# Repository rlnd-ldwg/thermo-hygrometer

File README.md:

# thermo-hygrometer
Thermo-Hygrometer based on DHT22, ATtiny13 and HD44780 compatible display  

v 1.0.3 wrong indication of negative temperature corrected,
pinout change for better use of IPS header for enhancements,
adaptations for the 16x1 display which uses addresses from a 2-line display
v 1.0.5 corrected error in pcb

To assemble the code, adjust the Makefile to your needs. You have then the following options:

* __make__  
assemble, link and convert to hex format
* __make flash__  
same as above but additionally flash the program
* __make list__  
assemble, link and create list file
* __make clean__  
delete all files except the source file
* __make showfuses__  
show the actual fuses from the mcu

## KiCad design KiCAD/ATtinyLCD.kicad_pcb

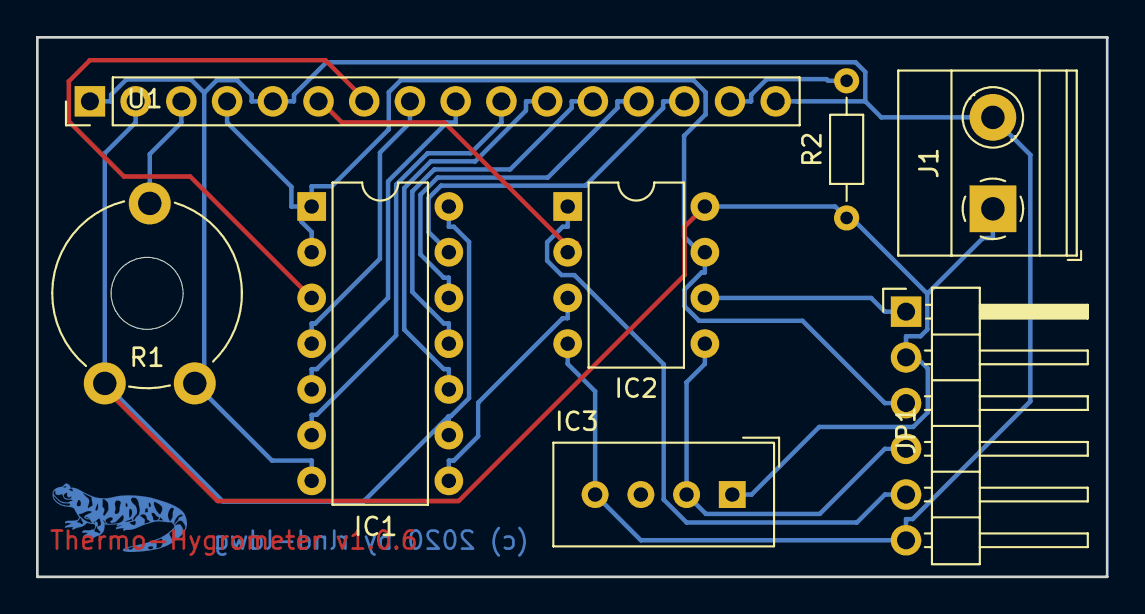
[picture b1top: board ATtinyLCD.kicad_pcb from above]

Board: 2 copper layers, 59.4 x 30.0 mm, 8 parts (0 on the bottom side), 18 nets.

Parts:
IC1: 74164; DIP-14_W7.62mm
IC2: ATtiny13-20PU; DIP-8_W7.62mm
IC3: DHT22; Aosong_DHT11_5.5x12.0_P2.54mm
J1: Screw_Terminal_01x02; TerminalBlock_Phoenix_MKDS-1,5-2-5.08_1x02_P5.08mm_Horizont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
JP1: AVR-ISP-6; PinHeader_1x06_P2.54mm_Horizontal
R1: 10k; Potentiometer_Piher_PT-10-V10_Vertical_Hole
R2: R; R_Axial_DIN0204_L3.6mm_D1.6mm_P7.62mm_Horizontal
U1: NHD-0420H1Z; PinHeader_1x16_P2.54mm_Vertical

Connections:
+5V: IC1.9, IC1.14, IC2.8, IC3.1, J1.1, JP1.2, R1.3, R2.1, U1.2
GND: IC1.7, IC2.4, IC3.4, J1.2, JP1.6, R1.1, U1.1, U1.5, U1.16
unnamed: IC1.1, IC1.2, IC2.7, JP1.3, U1.4
unnamed: IC1.3, U1.7
unnamed: IC1.4, U1.8
unnamed: IC1.5, U1.9
unnamed: IC1.6, U1.10
unnamed: IC1.8, IC2.3
unnamed: IC1.10, U1.11
unnamed: IC1.11, U1.12
unnamed: IC1.12, U1.13
unnamed: IC1.13, U1.14
unnamed: IC2.1, JP1.5
unnamed: IC2.2, U1.6
unnamed: IC2.5, IC3.2, JP1.4
unnamed: IC2.6, JP1.1
unnamed: R1.2, U1.3
unnamed: R2.2, U1.15

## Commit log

2020-01-28 v1.0.0
2020-02-01 v1.0.1 blinking hearbeat, error message
2020-02-01 Update Makefile
2020-02-07 v1.0.2
2020-02-11 v1.0.3
2020-03-30 v1.0.4
2020-12-29 v1.0.5 corrected error in pcb
2021-02-16 v1.0.6 correction of display errors of single-digit values, minor modifications on schematic and pcb

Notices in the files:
KiCAD/ATtinyLCD.kicad_pcb:
(c) 2020 by rlnd-ldwg
